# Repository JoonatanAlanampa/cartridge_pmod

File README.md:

# Cartridge Pmod

QSPI memory + audio Pmod for the TinyTapeout demo board and the ULX3S console
prototype. Drop-in compatible with the stock [QSPI Pmod](https://github.com/mole99/qspi-pmod)
pinout for any flash + single-PSRAM project; PMOD8 (uio[7]) carries sigma-delta
audio out instead of the second PSRAM chip select.

**v0.1 is at the fab**: ordered from JLCPCB 2026-07-20 (5 PCBs, 2 assembled),
tag [`fab-v0.1`](https://github.com/JoonatanAlanampa/cartridge_pmod/releases/tag/fab-v0.1). A self-checking ULX3S bring-up
bitstream is ready in [`fpga/`](fpga/README.md).

| | |
|---|---|
|  |  |
|  |  |

Full-size: [schematic PDF](cartridge-pmod.pdf) ·
[layout](img/pcb_layout.png) · [schematic PNG](img/schematic.png)

Remix of two Apache-2.0 designs:
- Memory section: [mole99/qspi-pmod](https://github.com/mole99/qspi-pmod) v2.2
  (W25Q128 16 MB flash + APS6404L 8 MB PSRAM, CONFIG jumper block, CS pull-ups)
- Audio section: [MichaelBell/tt-audio-pmod](https://github.com/MichaelBell/tt-audio-pmod)
  rev 1.0 (buffer + 2-stage RC low-pass + AC-coupled 3.5 mm jack), piezo branch dropped

## Pinout

| Pmod  | TinyTapeout | Function     | Note |
|-------|-------------|--------------|------|
| PMOD1 | uio[0]      | CS0 (Flash)  | CONFIG jumper to isolate |
| PMOD2 | uio[1]      | SD0/MOSI     |      |
| PMOD3 | uio[2]      | SD1/MISO     |      |
| PMOD4 | uio[3]      | SCK          | CONFIG jumper pair adds 22 pF clock delay |
| PMOD5 | uio[4]      | SD2          |      |
| PMOD6 | uio[5]      | SD3          |      |
| PMOD7 | uio[6]      | CS1 (PSRAM)  | CONFIG jumper to isolate |
| PMOD8 | uio[7]      | AUDIO (sigma-delta / PWM in) | CONFIG jumper to isolate; ≥200 kHz carrier recommended |

## Modes

- **Console / full**: all CONFIG jumpers closed — flash + PSRAM + audio at once
  (game-console cartridge: code XIP from flash, PSRAM work RAM, audio on uio[7]).
- **Universal audio Pmod**: CS0/CS1 jumpers open — memories held in standby by
  10 k pull-ups, board is a plain audio Pmod for any project driving uio[7].
- **QSPI-compat**: audio jumper open — behaves as the stock QSPI Pmod minus
  PSRAM B (projects using only CS0/CS1 work unmodified).

## Audio chain (from tt-audio-pmod)

PMOD8 → 74LVCE1G126 buffer (ferrite-filtered 3.3 V rail, OE tied high) →
120 Ω → 100 nF‖47 nF → 33 Ω → 100 nF (2-stage RC LPF) → 200 Ω trim shunt
(volume) → 47 µF AC coupling → PJ-320B jack (tip+ring mono, 470 Ω DC
reference). Buffer input is high-impedance: audio taps the bus without
loading it.

## Status

- [x] Schematic complete, netlist machine-verified against both upstream
      designs (`tools/netlist_check.py`)
- [x] PCB layout: 56.3 × 20.1 mm, fully placed + routed (largely via pcbnew
      scripting), ERC 0 / DRC 0-unconnected, 0 silk warnings; only remaining
      DRC errors are the intentional CONFIG cut-trace feature + one upstream
      starved-thermal
- [x] Fab: **ordered at JLCPCB 2026-07-20** (tag `fab-v0.1`) — 5 PCBs,
      2 assembled (Economic, incl. the THT Pmod header), $71.76 all-in;
      see [FABRICATION.md](FABRICATION.md) for the export recipe and the
      ordering lessons (J1 rotation, PSRAM LCSC number, PCBA remark)
- [x] ULX3S bring-up harness: flash/PSRAM ID + memory test + 440 Hz test
      tone + UART report, plug orientation autodetected; simulated in both
      orientations (cocotb + icarus), 898 LUTs — see [fpga/](fpga/README.md)
- [ ] Boards arrive (~3 weeks): run the
      [first-power-up checklist](fpga/README.md#first-power-up-checklist-per-board--do-steps-1-2-before-plugging-in)

## Tools

- `tools/sch_analyze.py <file.kicad_sch>` — list all top-level elements with
  positions
- `tools/netlist_check.py [file]` — derive and print the netlist from wire
  geometry (poor man's ERC)
- `tools/build_cartridge.py` — the one-shot surgery script that generated the
  schematic from the two reference designs (kept for provenance; do not re-run)

Reference designs are vendored read-only under `refs/`.

Licensed Apache-2.0 (same as both upstream designs).

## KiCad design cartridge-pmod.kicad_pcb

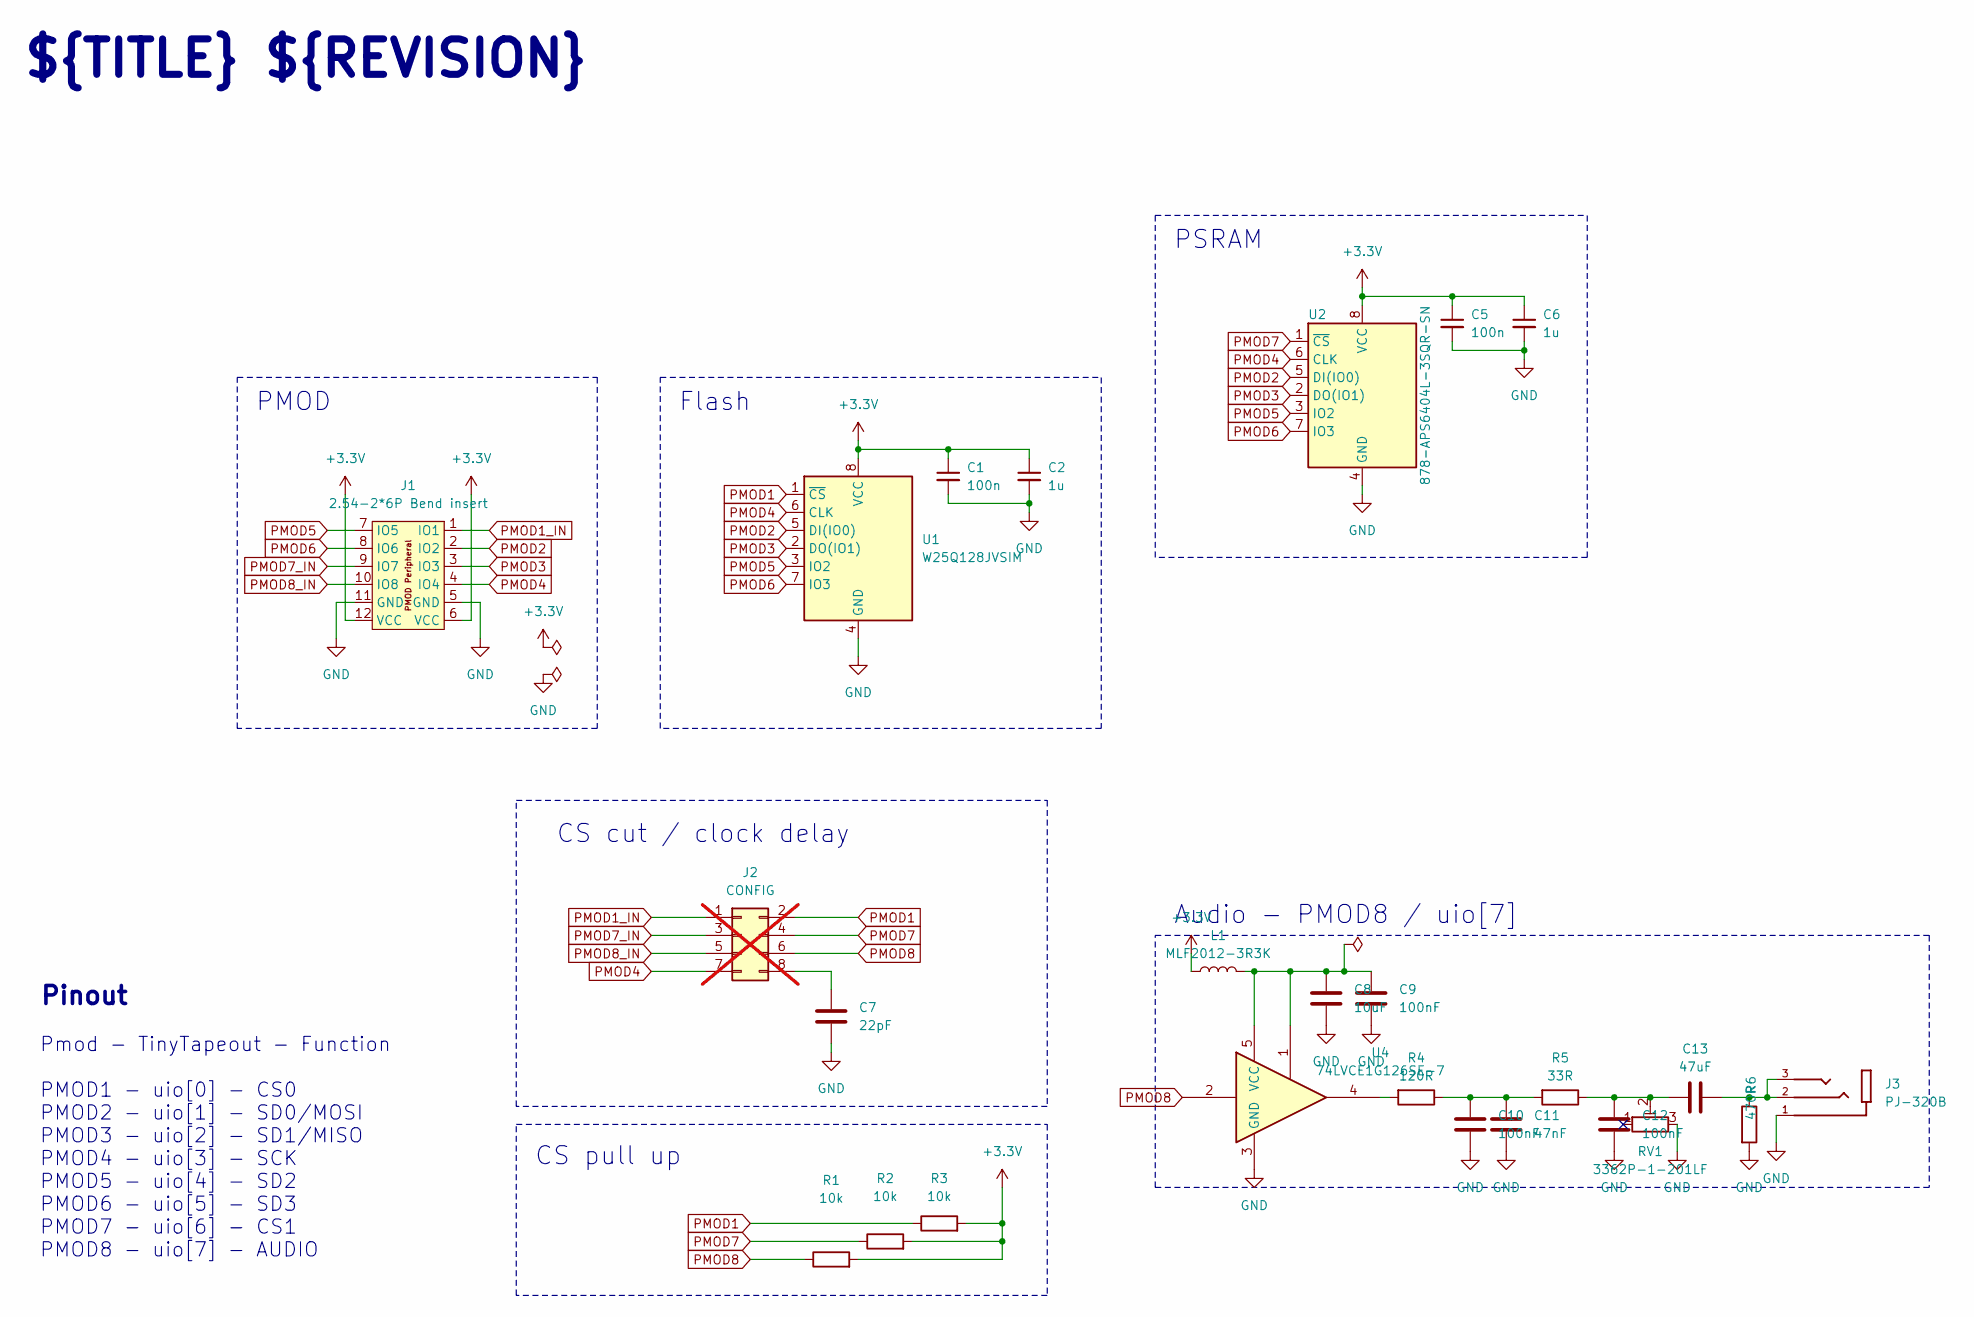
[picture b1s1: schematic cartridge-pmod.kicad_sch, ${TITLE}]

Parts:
C1, C5: 100n; C_0402_1005Metric; MPN 0402YC104KAT2A
C2, C6: 1u; C_0402_1005Metric; MPN C0402C105M9PAC
C7: 22pF; C_0402_1005Metric; MPN 0402CG220J500NT
C8: 10uF; C_0805_2012Metric; LCSC Part C15850
C9, C10, C12: 100nF; C_0603_1608Metric; LCSC Part C14663
C11: 47nF; C_0603_1608Metric; LCSC Part C1622
C13: 47uF; C_0805_2012Metric; LCSC Part C16780
J1: 2.54-2*6P Bend insert; PinHeader_2x06_P2.54mm_PMODPeriph2B; MPN 2.54-2*6P; LCSC Part C60565
J2: CONFIG; PinHeader_2x04_P2.54mm_Vertical; not fitted
J3: PJ-320B; BOOMELE_PJ-320B; LCSC Part C2884998
L1: MLF2012-3R3K; L_0805_2012Metric; LCSC Part C2941578
R1, R2, R3: 10k; R_0402_1005Metric; MPN 0402WGF1002TCE
R4: 120R; R_0603_1608Metric; LCSC Part C22787
R5: 33R; R_0603_1608Metric; LCSC Part C23140
R6: 470R; R_0603_1608Metric; LCSC Part C23179
RV1: 3362P-1-201LF; TRIM_3362P-1-102; LCSC Part C124581
U1: W25Q128JVSIM; SOIC-8_5.23x5.23mm_P1.27mm; MPN W25Q128JVSIM
U2: 878-APS6404L-3SQR-SN; SOP-8_3.9x4.9mm_P1.27mm; MPN APS6404L-3SQR-SN
U4: 74LVCE1G126SE-7; SOT-353_SC-70-5; LCSC Part C842506

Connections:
+3.3V: C1.1, C2.1, C5.1, C6.1, J1.6 (VCC), J1.12 (VCC), L1.1, R1.2, R2.2, R3.2, U1.8 (VCC), U2.8 (VCC)
AUDIO_BUF: R4.2, U4.4
AUDIO_N1: C10.1, C11.1, R4.1, R5.2
AUDIO_N2: C12.1, C13.2, R5.1, RV1.2
AUDIO_OUT: C13.1, J3.2, J3.3, R6.1
AUDIO_VCCA: C8.1, C9.1, L1.2, U4.1, U4.5 (VCC)
GND: C1.2, C2.2, C5.2, C6.2, C7.1, C8.2, C9.2, C10.2, C11.2, C12.2, J1.5 (GND), J1.11 (GND), J3.1, R6.2, RV1.3, U1.4 (GND), U2.4 (GND), U4.3 (GND)
unnamed: C7.2, J2.8
PMOD1: J2.2, R3.1, U1.1 (~CS)
PMOD1_IN: J1.1 (IO1), J2.1
PMOD2: J1.2 (IO2), U1.5 (DI(IO0)), U2.5 (DI(IO0))
PMOD3: J1.3 (IO3), U1.2 (DO(IO1)), U2.2 (DO(IO1))
PMOD4: J1.4 (IO4), J2.7, U1.6 (CLK), U2.6 (CLK)
PMOD5: J1.7 (IO5), U1.3 (IO2), U2.3 (IO2)
PMOD6: J1.8 (IO6), U1.7 (IO3), U2.7 (IO3)
PMOD7: J2.4, R2.1, U2.1 (~CS)
PMOD7_IN: J1.9 (IO7), J2.3
PMOD8: J2.6, R1.1, U4.2
PMOD8_IN: J1.10 (IO8), J2.5

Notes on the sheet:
CS cut / clock delay
PMOD
Flash
CS pull up
${TITLE} ${REVISION}
PSRAM
Pmod - TinyTapeout - Function PMOD1 - uio[0] - CS0 PMOD2 - uio[1] - SD0/MOSI PMOD3 - uio[2] - SD1/MISO PMOD4 - uio[3] - SCK PMOD5 - uio[4] - SD2 PMOD6 - uio[5] - SD3 PMOD7 - uio[6] - CS1 PMOD8 - uio[7] - AUDIO
Pinout
Audio - PMOD8 / uio[7]

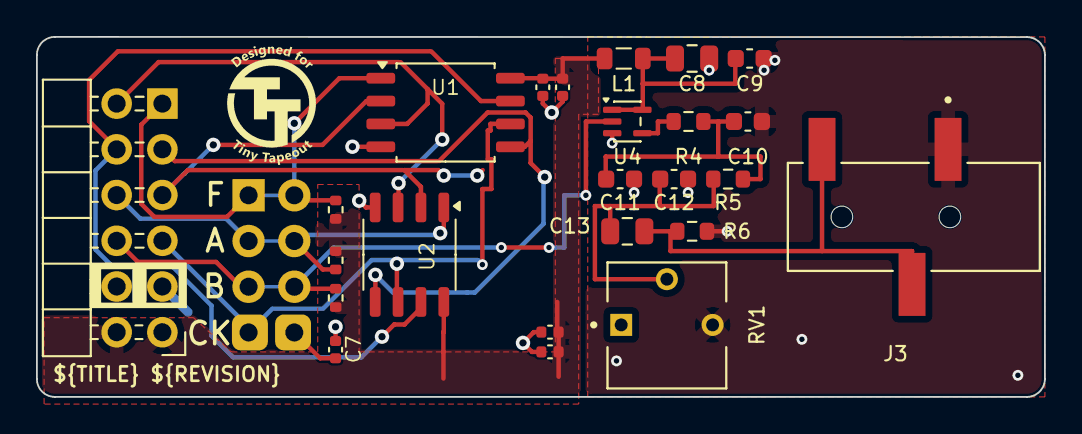
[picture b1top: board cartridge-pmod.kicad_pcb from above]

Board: 2 copper layers, 56.0 x 20.0 mm, 25 parts (0 on the bottom side), 19 nets.

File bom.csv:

"Reference","Value","Footprint","QUANTITY","LCSC Part","MPN"
"C1,C5","100n","Capacitor_SMD:C_0402_1005Metric","2","","0402YC104KAT2A"
"C2,C6","1u","Capacitor_SMD:C_0402_1005Metric","2","","C0402C105M9PAC"
"C7","22pF","Capacitor_SMD:C_0402_1005Metric","1","","0402CG220J500NT"
"C8","10uF","Capacitor_SMD:C_0805_2012Metric","1","C15850",""
"C9,C10,C12","100nF","Capacitor_SMD:C_0603_1608Metric","3","C14663",""
"C11","47nF","Capacitor_SMD:C_0603_1608Metric","1","C1622",""
"C13","47uF","Capacitor_SMD:C_0805_2012Metric","1","C16780",""
"J1","2.54-2*6P Bend insert","tt:PinHeader_2x06_P2.54mm_PMODPeriph2B","1","C60565","2.54-2*6P"
"J2","CONFIG","Connector_PinHeader_2.54mm:PinHeader_2x04_P2.54mm_Vertical","1","",""
"J3","PJ-320B","LCSC:BOOMELE_PJ-320B","1","C2884998",""
"L1","MLF2012-3R3K","Inductor_SMD:L_0805_2012Metric","1","C2941578",""
"R1-R3","10k","Resistor_SMD:R_0402_1005Metric","3","","0402WGF1002TCE"
"R4","120R","Resistor_SMD:R_0603_1608Metric","1","C22787",""
"R5","33R","Resistor_SMD:R_0603_1608Metric","1","C23140",""
"R6","470R","Resistor_SMD:R_0603_1608Metric","1","C23179",""
"RV1","3362P-1-201LF","LCSC:TRIM_3362P-1-102","1","C124581",""
"U1","W25Q128JVSIM","Package_SO:SOIC-8_5.23x5.23mm_P1.27mm","1","","W25Q128JVSIM"
"U2","878-APS6404L-3SQR-SN","Package_SO:SOP-8_3.9x4.9mm_P1.27mm","1","","APS6404L-3SQR-SN"
"U4","74LVCE1G126SE-7","Package_TO_SOT_SMD:SOT-353_SC-70-5","1","C842506",""
